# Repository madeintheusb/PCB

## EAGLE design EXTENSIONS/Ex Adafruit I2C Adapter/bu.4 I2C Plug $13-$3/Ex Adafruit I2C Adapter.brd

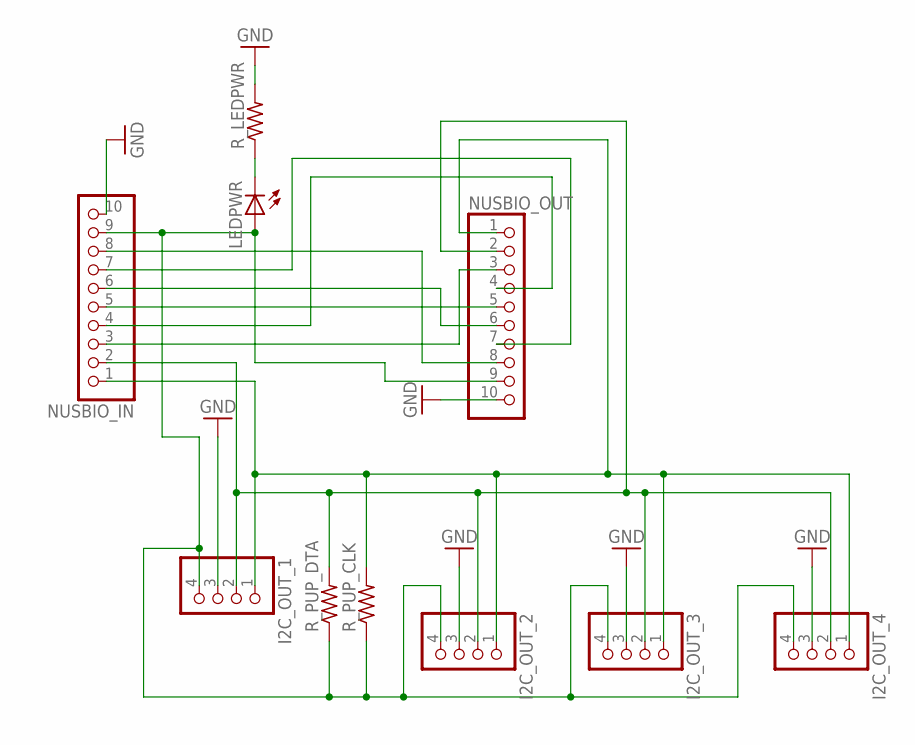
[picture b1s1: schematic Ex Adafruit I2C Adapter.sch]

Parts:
I2C_OUT_1, I2C_OUT_2, I2C_OUT_3, I2C_OUT_4: PINHD-1X4; 1X04
LEDPWR: LEDCHIPLED_0805; CHIPLED_0805
NUSBIO_IN: PINHD-1X10; 1X10-BIG
NUSBIO_OUT: PINHD-1X10; 1X10-BIG
R_LEDPWR: R-US_R0805; R0805
R_PUP_CLK: R-US_R0805; R0805
R_PUP_DTA: R-US_R0805; R0805

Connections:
GND: I2C_OUT_1.3, I2C_OUT_2.3, I2C_OUT_3.3, I2C_OUT_4.3, NUSBIO_IN.10, NUSBIO_OUT.10, R_LEDPWR.2
unnamed: LEDPWR.C, R_LEDPWR.1
unnamed: I2C_OUT_1.4, I2C_OUT_2.4, I2C_OUT_3.4, I2C_OUT_4.4, LEDPWR.A, NUSBIO_IN.9, NUSBIO_OUT.9, R_PUP_CLK.1, R_PUP_DTA.1
unnamed: NUSBIO_IN.6, NUSBIO_OUT.6
unnamed: NUSBIO_IN.5, NUSBIO_OUT.5
unnamed: NUSBIO_IN.3, NUSBIO_OUT.3
unnamed: NUSBIO_IN.8, NUSBIO_OUT.8
unnamed: NUSBIO_IN.4, NUSBIO_OUT.4
unnamed: NUSBIO_IN.7, NUSBIO_OUT.7
unnamed: I2C_OUT_1.1, I2C_OUT_2.1, I2C_OUT_3.1, I2C_OUT_4.1, NUSBIO_IN.1, NUSBIO_OUT.1, R_PUP_CLK.2
unnamed: I2C_OUT_1.2, I2C_OUT_2.2, I2C_OUT_3.2, I2C_OUT_4.2, NUSBIO_IN.2, NUSBIO_OUT.2, R_PUP_DTA.2

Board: 2 copper layers, 10 parts (0 on the bottom side), 11 nets, no tracks yet.

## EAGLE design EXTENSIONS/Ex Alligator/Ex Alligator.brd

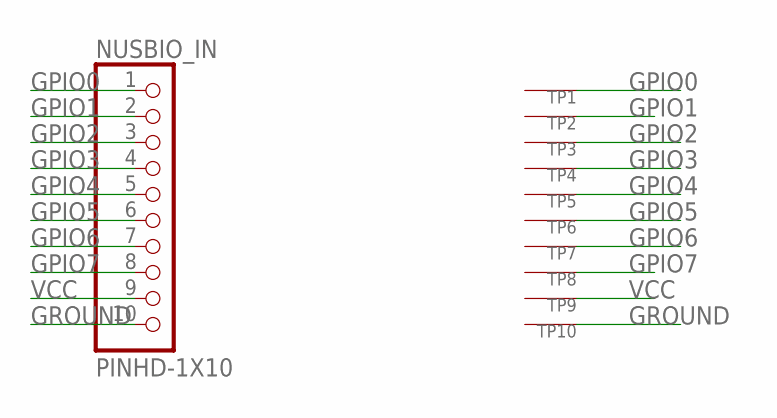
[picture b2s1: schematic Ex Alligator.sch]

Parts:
NUSBIO_IN: PINHD-1X10; 1X10-BIG
TP1, TP2, TP3, TP4, TP5, TP6, TP7, TP8, TP9, TP10: SEWTAPBIG; BIGTAP

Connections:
GPIO0: NUSBIO_IN.1, TP1.P$1
GPIO1: NUSBIO_IN.2, TP2.P$1
GPIO2: NUSBIO_IN.3, TP3.P$1
GPIO3: NUSBIO_IN.4, TP4.P$1
GPIO4: NUSBIO_IN.5, TP5.P$1
GPIO5: NUSBIO_IN.6, TP6.P$1
GPIO6: NUSBIO_IN.7, TP7.P$1
GPIO7: NUSBIO_IN.8, TP8.P$1
GROUND: NUSBIO_IN.10, TP10.P$1
VCC: NUSBIO_IN.9, TP9.P$1

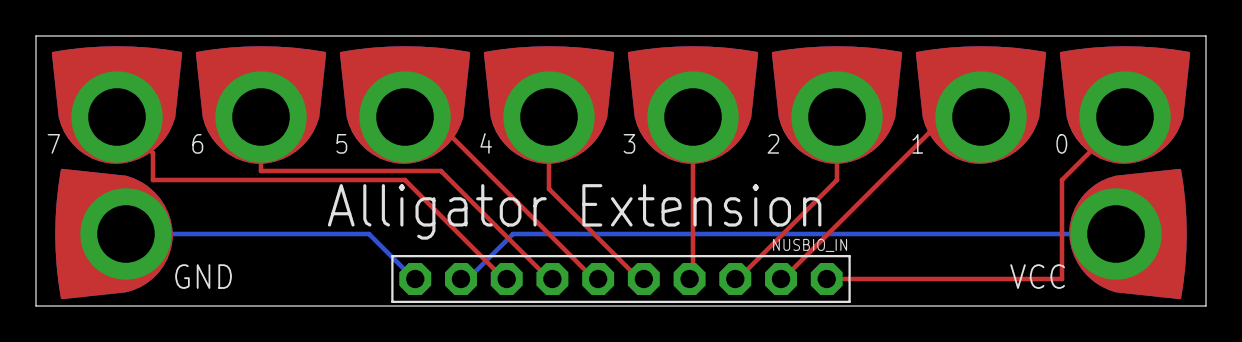
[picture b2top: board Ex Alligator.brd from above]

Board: 2 copper layers, 65.0 x 15.0 mm, 11 parts (0 on the bottom side), 10 nets.

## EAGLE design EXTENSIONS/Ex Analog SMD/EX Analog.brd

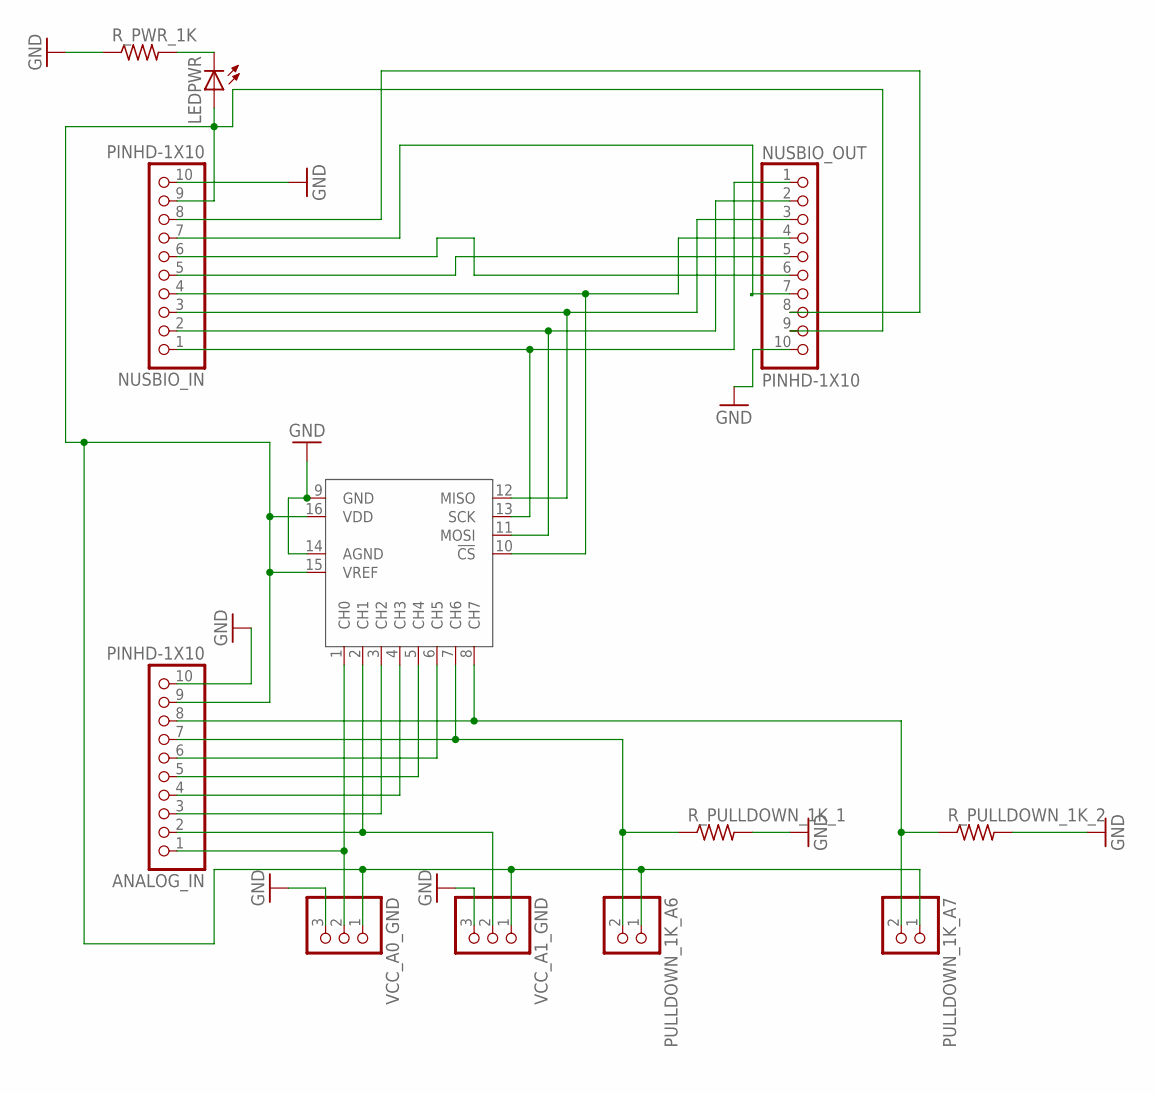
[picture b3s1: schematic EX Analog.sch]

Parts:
ANALOG_IN: PINHD-1X10; 1X10-BIG
LEDPWR: LEDCHIPLED_0805; CHIPLED_0805
NUSBIO_IN: PINHD-1X10; 1X10-BIG
NUSBIO_OUT: PINHD-1X10; 1X10-BIG
PULLDOWN_1K_A6, PULLDOWN_1K_A7: PINHD-1X2; 1X02
R_PULLDOWN_1K_1, R_PULLDOWN_1K_2: R-US_R0805; R0805
R_PWR_1K: R-US_R0805; R0805
U$1: MCP3008SL; SO16
VCC_A0_GND, VCC_A1_GND: PINHD-1X3; 1X03

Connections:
GND: ANALOG_IN.10, NUSBIO_IN.10, NUSBIO_OUT.10, R_PULLDOWN_1K_1.2, R_PULLDOWN_1K_2.2, R_PWR_1K.1, U$1.9 (GND), U$1.14 (AGND), VCC_A0_GND.3, VCC_A1_GND.3
unnamed: NUSBIO_IN.1, NUSBIO_OUT.1, U$1.13 (SCK)
unnamed: NUSBIO_IN.2, NUSBIO_OUT.2, U$1.11 (MOSI)
unnamed: NUSBIO_IN.3, NUSBIO_OUT.3, U$1.12 (MISO)
unnamed: NUSBIO_IN.5, NUSBIO_OUT.5
unnamed: NUSBIO_IN.4, NUSBIO_OUT.4, U$1.10 (!CS)
unnamed: LEDPWR.C, R_PWR_1K.2
unnamed: NUSBIO_IN.6, NUSBIO_OUT.6
unnamed: NUSBIO_IN.7, NUSBIO_OUT.7
unnamed: NUSBIO_IN.8, NUSBIO_OUT.8
unnamed: ANALOG_IN.1, U$1.1 (CH0), VCC_A0_GND.2
unnamed: ANALOG_IN.2, U$1.2 (CH1), VCC_A1_GND.2
unnamed: ANALOG_IN.3, U$1.3 (CH2)
unnamed: ANALOG_IN.4, U$1.4 (CH3)
unnamed: ANALOG_IN.6, U$1.6 (CH5)
unnamed: ANALOG_IN.7, PULLDOWN_1K_A6.2, R_PULLDOWN_1K_1.1, U$1.7 (CH6)
unnamed: ANALOG_IN.8, PULLDOWN_1K_A7.2, R_PULLDOWN_1K_2.1, U$1.8 (CH7)
unnamed: ANALOG_IN.5, U$1.5 (CH4)
unnamed: ANALOG_IN.9, LEDPWR.A, NUSBIO_IN.9, NUSBIO_OUT.9, PULLDOWN_1K_A6.1, PULLDOWN_1K_A7.1, U$1.15 (VREF), U$1.16 (VDD), VCC_A0_GND.1, VCC_A1_GND.1

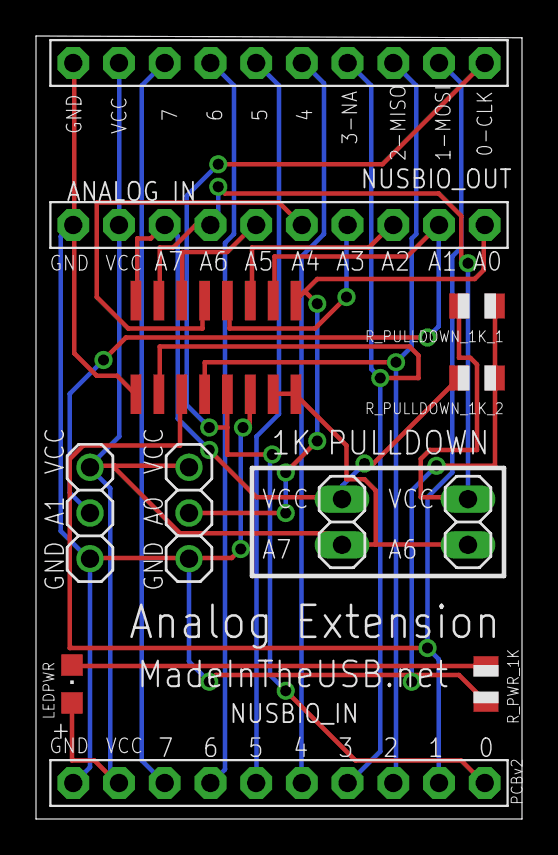
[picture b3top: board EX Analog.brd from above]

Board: 2 copper layers, 27.0 x 43.5 mm, 12 parts (0 on the bottom side), 19 nets.
